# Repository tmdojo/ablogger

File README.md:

# ablogger
Log A/B survey at certain interval

# Description

This is a tool to record a person's feelings at one hour interval.
The aim is to collect emotional labels which are to be studied together with data from sensors such as health tracker.

The device would beep at certain interval, say every hour, prompting user to push A or B button. Upon pressing a button, it records the button with time stamp.

# Hardware components

* Adafruit Feather M0 Adaloger:
* piezo buzzer: play sound for input queue
* two push buttons: Select A or B
* slide switch: Turn on/off sound
* uSD card: Record in csv file

# Schematics

To be added...

## for v0.1

| Feather | component | Note |
| A0 | Piezo | The other leg is connected to GND |
| 11 | Button A | The other leg is connected to GND |
| 12 | Button B | The other leg is connected to GND |
| 10 | Slide switch | Middle leg is connected to GND and the other left floating |
| 4 | SDCS | CS for SD card of Adafruit Adalogger M0 |

## for v1.0 PCB

| Feather | component | Note |
| A0 | Piezo | The other leg is connected to GND |
| 11 | Button A | The other leg is connected to GND |
| 12 | Button B | The other leg is connected to GND |
| 10 | Slide switch | Middle leg is connected to GND and the other left floating |
| 5 | SDCS | CS for SD card of adafruit Adalogger FeatherWing|
| 9(A7) | battery monitor | Feather buit-in voltage divider |
| 6 | RTC INT | RTC INT from adafruit Adalogger FeatherWing <-- Not used|

## for v1.1 PCB (to be designed)

| Feather | component | Note |
| A0 | Piezo | The other leg is connected to GND |
| 11 | Button A | The other leg is connected to GND |
| 12 | Button B | The other leg is connected to GND |
| 5 | Slide switch | Middle leg is connected to GND and the other left floating |
| 10 | SDCS | CS for SD card of adafruit Adalogger FeatherWing |
| 9 | battery monitor | Feather buit-in voltage divider |
| 6 | RTC INT | RTC INT from adafruit Adalogger FeatherWing|

Note that pins for SDCS and Slide switch is swapped from v1.0 (to match default of Adafruit Adalogger FeatherWing)

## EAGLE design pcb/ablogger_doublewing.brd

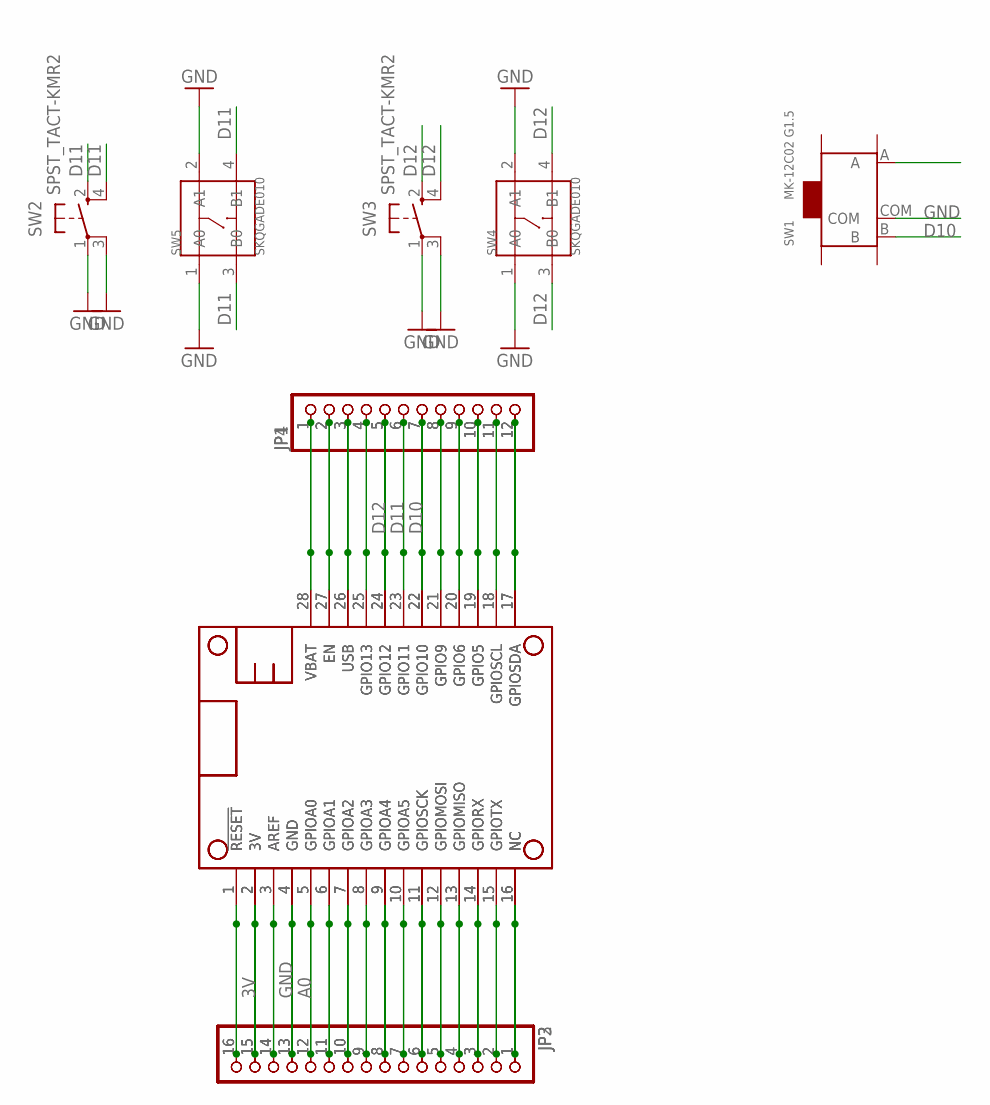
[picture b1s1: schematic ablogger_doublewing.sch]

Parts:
JP1, JP4: HEADER-1X1276MIL; 1X12_ROUND_76MIL
JP2, JP3: HEADER-1X16_76MIL; 1X16_ROUND_76MIL
MS1, MS2: FEATHERWING_NODIM; FEATHERWING_DIM
SW1: MK-12C02 G1.5; SW7-SMD-L6.7X2.7X3.2MM
SW2, SW3: SPST_TACT-KMR2; KMR2
SW4, SW5: SKQGADE010; SW4-SMD-5.2X5.2X1.5MM

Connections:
3V: JP2.15, JP3.15, MS1.2 (3V), MS2.2 (3V)
A0: JP2.12, JP3.12, MS1.5 (GPIOA0), MS2.5 (GPIOA0)
D10: JP1.7, JP4.7, MS1.22 (GPIO10), MS2.22 (GPIO10), SW1.B
D11: JP1.6, JP4.6, MS1.23 (GPIO11), MS2.23 (GPIO11), SW2.2 (S), SW2.4 (S1), SW5.3 (B0), SW5.4 (B1)
D12: JP1.5, JP4.5, MS1.24 (GPIO12), MS2.24 (GPIO12), SW3.2 (S), SW3.4 (S1), SW4.3 (B0), SW4.4 (B1)
GND: JP2.13, JP3.13, MS1.4 (GND), MS2.4 (GND), SW1.COM, SW2.1, SW2.3 (P1), SW3.1, SW3.3 (P1), SW4.1 (A0), SW4.2 (A1), SW5.1 (A0), SW5.2 (A1)
unnamed: JP1.2, JP4.2, MS1.27 (EN), MS2.27 (EN)
unnamed: JP2.1, JP3.1, MS1.16 (NC), MS2.16 (NC)
unnamed: JP1.4, JP4.4, MS1.25 (GPIO13), MS2.25 (GPIO13)
unnamed: JP2.2, JP3.2, MS1.15 (GPIOTX), MS2.15 (GPIOTX)
unnamed: JP2.3, JP3.3, MS1.14 (GPIORX), MS2.14 (GPIORX)
unnamed: JP2.4, JP3.4, MS1.13 (GPIOMISO), MS2.13 (GPIOMISO)
unnamed: JP2.5, JP3.5, MS1.12 (GPIOMOSI), MS2.12 (GPIOMOSI)
unnamed: JP2.6, JP3.6, MS1.11 (GPIOSCK), MS2.11 (GPIOSCK)
unnamed: JP2.7, JP3.7, MS1.10 (GPIOA5), MS2.10 (GPIOA5)
unnamed: JP2.8, JP3.8, MS1.9 (GPIOA4), MS2.9 (GPIOA4)
unnamed: JP2.9, JP3.9, MS1.8 (GPIOA3), MS2.8 (GPIOA3)
unnamed: JP2.10, JP3.10, MS1.7 (GPIOA2), MS2.7 (GPIOA2)
unnamed: JP2.11, JP3.11, MS1.6 (GPIOA1), MS2.6 (GPIOA1)
unnamed: JP2.14, JP3.14, MS1.3 (AREF), MS2.3 (AREF)
unnamed: JP2.16, JP3.16, MS1.1 (!RESET), MS2.1 (!RESET)
unnamed: JP1.8, JP4.8, MS1.21 (GPIO9), MS2.21 (GPIO9)
unnamed: JP1.9, JP4.9, MS1.20 (GPIO6), MS2.20 (GPIO6)
unnamed: JP1.10, JP4.10, MS1.19 (GPIO5), MS2.19 (GPIO5)
unnamed: JP1.11, JP4.11, MS1.18 (GPIOSCL), MS2.18 (GPIOSCL)
unnamed: JP1.12, JP4.12, MS1.17 (GPIOSDA), MS2.17 (GPIOSDA)
USB: JP1.3, JP4.3, MS1.26 (USB), MS2.26 (USB)
VBAT: JP1.1, JP4.1, MS1.28 (VBAT), MS2.28 (VBAT)

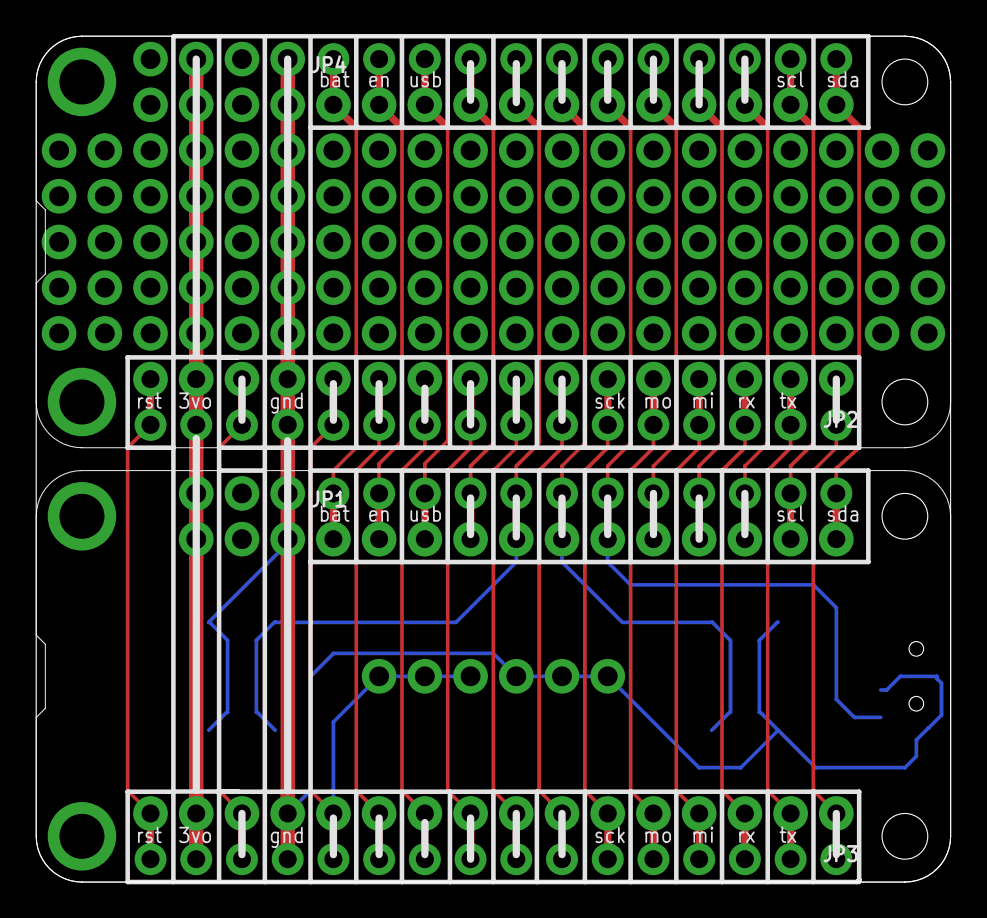
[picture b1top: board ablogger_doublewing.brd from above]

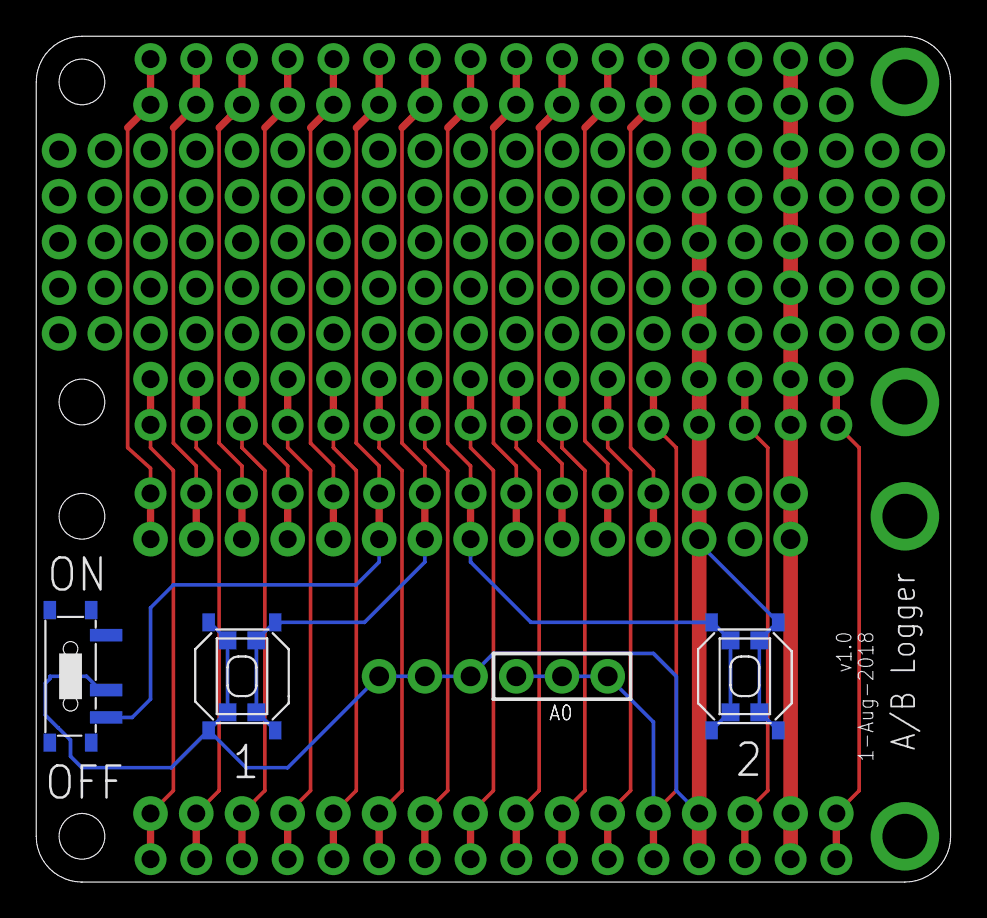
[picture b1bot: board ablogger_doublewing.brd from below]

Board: 2 copper layers, 50.8 x 47.0 mm, 11 parts (5 on the bottom side), 28 nets.

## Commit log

2018-07-10 collect examples
2018-07-16 1st usable version
2018-07-16 Use sheet_music.h to define songs
2018-08-07 v1.0 pcb pinouts
2018-08-10 start implementing interrupt pin
2018-08-10 Under mod to implement state machine in loop
2018-08-19 1st release with v1.0 HW
2018-08-19 Add pcb files
2018-08-27 Change to require pressing A button to update RTC so that normal reset doesn't update. Initialise SD and File object everytime logging is required.
